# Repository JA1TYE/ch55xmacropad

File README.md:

# CH55xで作るマクロパッド

## 概要
[#MakePCBA 第2回](https://makepcba02.peatix.com/)で紹介した15キーのマクロパッドの設計データです。

## ディレクトリ構成
- docs/:README用の画像など
- firmware/:キーボード用のファームウェアです。[CH55xduino](https://github.com/DeqingSun/ch55xduino)用のスケッチファイルになっています。
- hardware/pcb/:回路図と基板、部品実装用のデータです。KiCAD用です。

## ライセンス
LGPL-2.1ライセンスに従います。

- firmware/ディレクトリのソースのうちch55xmacropad.inoはCH55xduinoのサンプルスケッチをベースにしています。
- firmware/src/内のソースはCH55xduinoのサンプルスケッチに付属のソースをそのまま流用しています。

## 作者
- JA1TYE/Ryota Suzuki([@JA1TYE](https://twitter.com/JA1TYE))
- Webサイト：[https://t-techlab.com](https://t-techlab.com)

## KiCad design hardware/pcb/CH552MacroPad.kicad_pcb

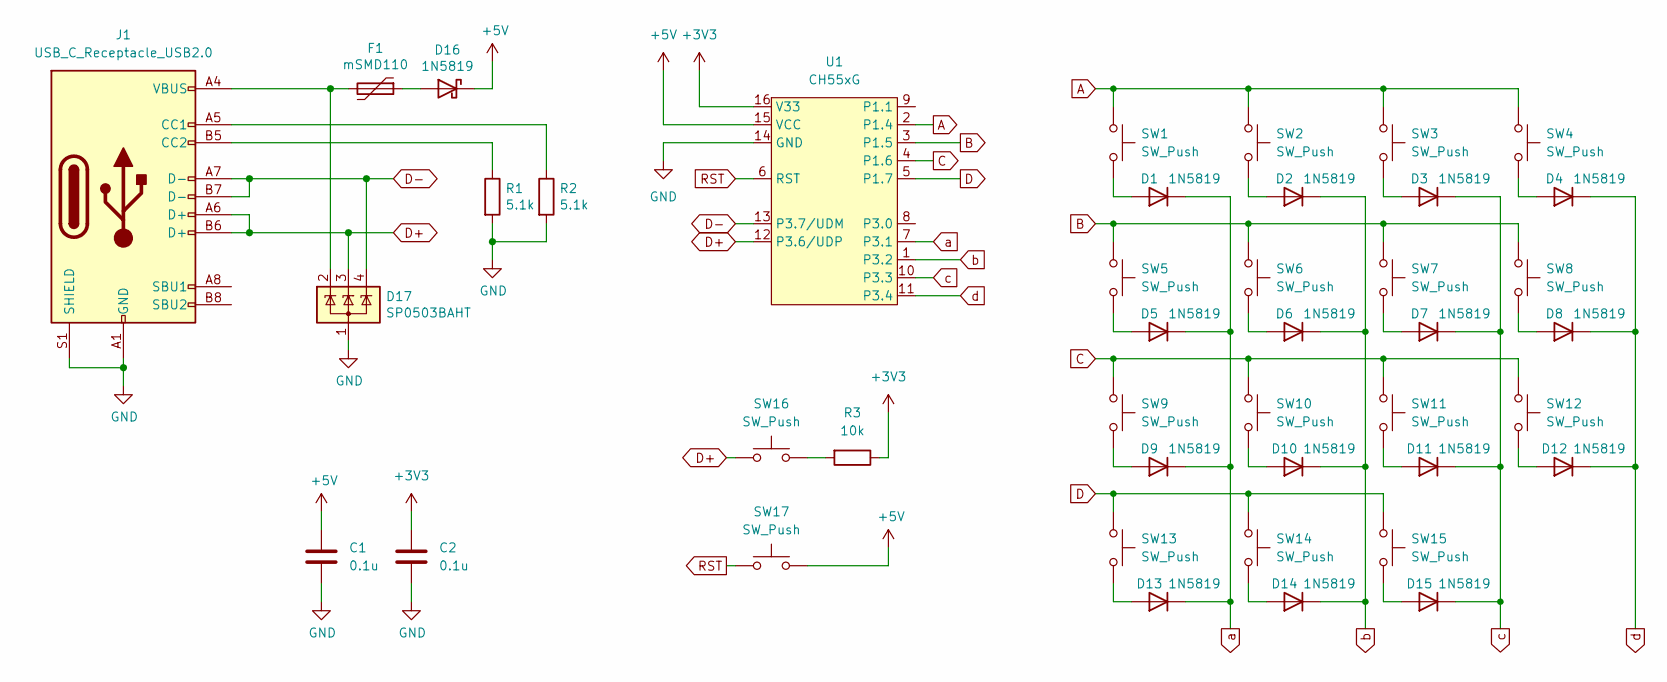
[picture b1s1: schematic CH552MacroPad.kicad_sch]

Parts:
C1, C2: 0.1u; C_0402_1005Metric
D1, D2, D3, D4, D5, D6, D7, D8, D9, D10, D11, D12, D13, D14, D15, D16: 1N5819; D_SOD-123
D17: SP0503BAHT; SOT-143
F1: mSMD110; Fuse_1812_4532Metric
J1: USB_C_Receptacle_USB2.0; USB_C_2.0
R1, R2: 5.1k; R_0402_1005Metric
R3: 10k; R_0402_1005Metric
SW1, SW2, SW3, SW4, SW5, SW6, SW7, SW8, SW9, SW10, SW11, SW12, SW13, SW14, SW15: SW_Push; SW_Cherry_MX_1.00u_PCB
SW16, SW17: SW_Push; SW_Push_SPST_NO_Alps_SKRK
U1: CH55xG; SOIC-16_3.9x9.9mm_P1.27mm

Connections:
+3V3: C2.1, R3.1, U1.16 (V33)
+5V: C1.1, D16.1 (K), SW17.2, U1.15 (VCC)
A: SW1.1, SW2.1, SW3.1, SW4.1, U1.2 (P1.4)
B: SW5.1, SW6.1, SW7.1, SW8.1, U1.3 (P1.5)
C: SW9.1, SW10.1, SW11.1, SW12.1, U1.4 (P1.6)
D: SW13.1, SW14.1, SW15.1, U1.5 (P1.7)
D+: D17.3 (K), J1.A6 (D+), J1.B6 (D+), SW16.1, U1.12 (P3.6/UDP)
D-: D17.4 (K), J1.A7 (D-), J1.B7 (D-), U1.13 (P3.7/UDM)
GND: C1.2, C2.2, D17.1 (A), J1.A1 (GND), J1.A12 (GND), J1.B1 (GND), J1.B12 (GND), J1.S1 (SHIELD), R1.2, R2.2, U1.14 (GND)
unnamed: D1.2 (A), SW1.2
unnamed: D2.2 (A), SW2.2
unnamed: D3.2 (A), SW3.2
unnamed: D4.2 (A), SW4.2
unnamed: D5.2 (A), SW5.2
unnamed: D6.2 (A), SW6.2
unnamed: D7.2 (A), SW7.2
unnamed: D8.2 (A), SW8.2
unnamed: D9.2 (A), SW9.2
unnamed: D10.2 (A), SW10.2
unnamed: D11.2 (A), SW11.2
unnamed: D12.2 (A), SW12.2
unnamed: D13.2 (A), SW13.2
unnamed: D14.2 (A), SW14.2
unnamed: D15.2 (A), SW15.2
unnamed: D16.2 (A), F1.1
unnamed: D17.2 (K), F1.2, J1.A4 (VBUS), J1.A9 (VBUS), J1.B4 (VBUS), J1.B9 (VBUS)
unnamed: J1.A5 (CC1), R2.1
unnamed: J1.B5 (CC2), R1.1
unnamed: R3.2, SW16.2
RST: SW17.1, U1.6 (RST)
a: D1.1 (K), D5.1 (K), D9.1 (K), D13.1 (K), U1.7 (P3.1)
b: D2.1 (K), D6.1 (K), D10.1 (K), D14.1 (K), U1.1 (P3.2)
c: D3.1 (K), D7.1 (K), D11.1 (K), D15.1 (K), U1.10 (P3.3)
d: D4.1 (K), D8.1 (K), D12.1 (K), U1.11 (P3.4)

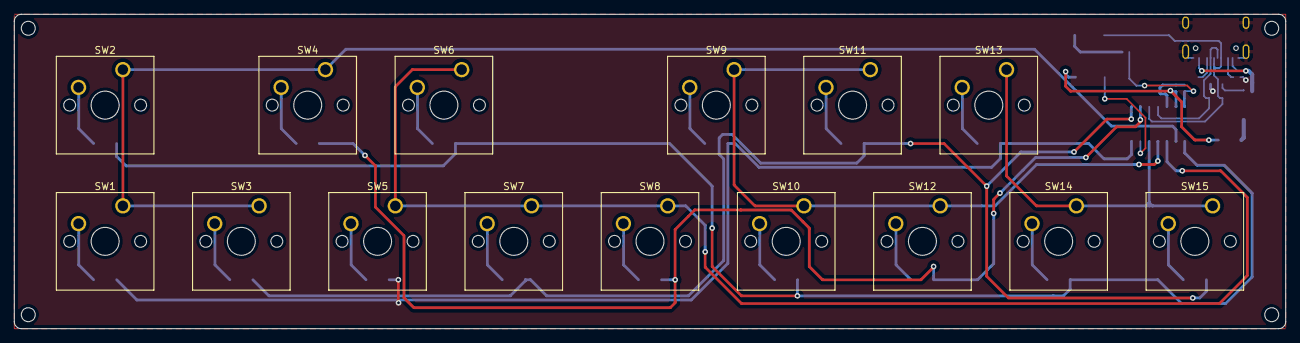
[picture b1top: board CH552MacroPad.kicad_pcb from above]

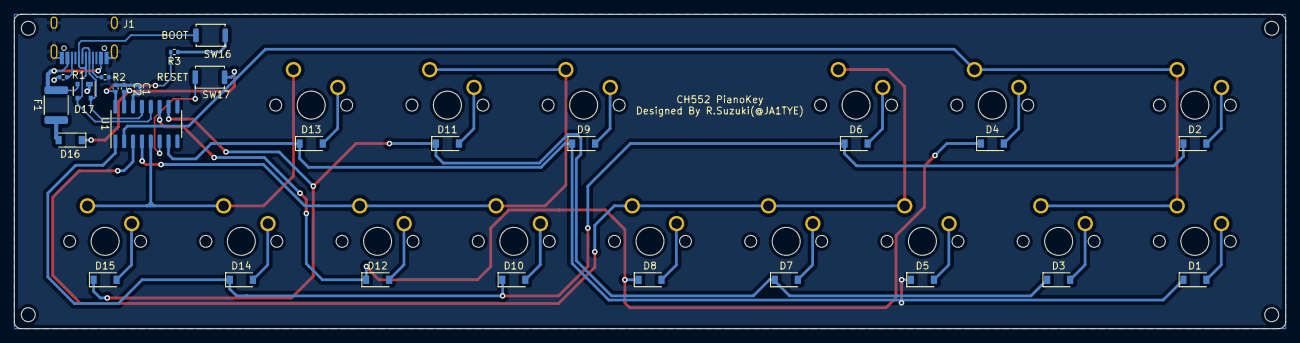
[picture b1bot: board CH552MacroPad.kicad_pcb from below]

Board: 2 copper layers, 182.0 x 45.0 mm, 42 parts (27 on the bottom side), 34 nets.

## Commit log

2022-09-11 fix README.md
